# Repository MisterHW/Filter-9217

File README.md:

# Filter-9217

A pluggable input filter adapter to mitigate CM and DM noise on 4-wire RTD scanner modules like NI-9217.

## Schematic

## Board

## Connectors

For part names and mating connector see 
[Filter-9217-1A_sch.pdf](Filter-9217-1A/Filter-9217-1A_sch.pdf).

## Revisions

- 2021-03-09: Rev-1A released with corrected silk screen orientation (was upside-down when module mounted horizontally)

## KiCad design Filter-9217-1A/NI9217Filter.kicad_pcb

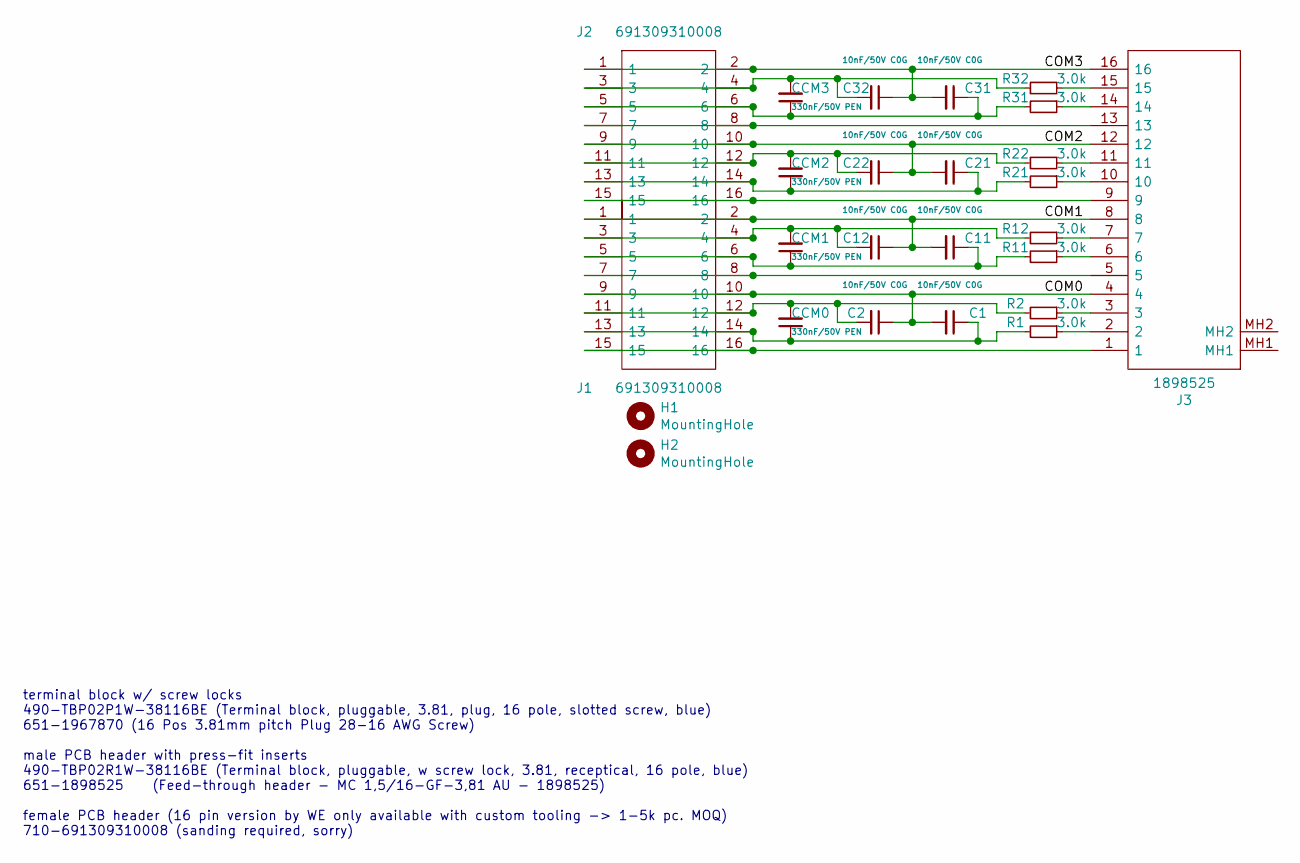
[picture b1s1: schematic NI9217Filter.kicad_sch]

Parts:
C1, C2, C11, C12, C21, C22, C31, C32: 10nF/50V C0G; C_0805_2012Metric; Mouser 791-0805N103J500CT
CCM0, CCM1, CCM2, CCM3: 330nF/50V PEN; C_2220_5650Metric; Mouser 80-LDECD3330KA5N00
H1, H2: MountingHole; MountingHole_3mm_Pad
J1, J2: 691309310008; Manufacturer_Part_Number 691309310008; Mouser Part Number 710-691309310008
J3: 1898525; Manufacturer_Part_Number 1898525; Mouser Part Number 651-1898525
R1, R2, R11, R12, R21, R22, R31, R32: 3.0k; R_0805_2012Metric; Mouser 667-ERJ-S06F3001V

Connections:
/COM0: C1.2, C2.1, J2.9, J2.10, J3.4
/COM1: C11.2, C12.1, J2.1, J2.2, J3.8
/COM2: C21.2, C22.1, J1.9, J1.10, J3.12
/COM3: C31.2, C32.1, J1.1, J1.2, J3.16
unnamed: C1.1, CCM0.1, J2.13, J2.14, R1.2
unnamed: C2.2, CCM0.2, J2.11, J2.12, R2.2
unnamed: C11.1, CCM1.1, J2.5, J2.6, R11.2
unnamed: C12.2, CCM1.2, J2.3, J2.4, R12.2
unnamed: C21.1, CCM2.1, J1.13, J1.14, R21.2
unnamed: C22.2, CCM2.2, J1.11, J1.12, R22.2
unnamed: C31.1, CCM3.1, J1.5, J1.6, R31.2
unnamed: C32.2, CCM3.2, J1.3, J1.4, R32.2
unnamed: J1.7, J1.8, J3.13
unnamed: J1.15, J1.16, J3.9
unnamed: J2.7, J2.8, J3.5
unnamed: J2.15, J2.16, J3.1
unnamed: J3.2, R1.1
unnamed: J3.3, R2.1
unnamed: J3.6, R11.1
unnamed: J3.7, R12.1
unnamed: J3.10, R21.1
unnamed: J3.11, R22.1
unnamed: J3.14, R31.1
unnamed: J3.15, R32.1

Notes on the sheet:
terminal block w/ screw locks 490-TBP02P1W-38116BE (Terminal block, pluggable, 3.81, plug, 16 pole, slotted screw, blue) 651-1967870 (16 Pos 3.81mm pitch Plug 28-16 AWG Screw) male PCB header with press-fit inserts 490-TBP02R1W-38116BE (Terminal block, pluggable, w screw lock, 3.81, receptical, 16 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

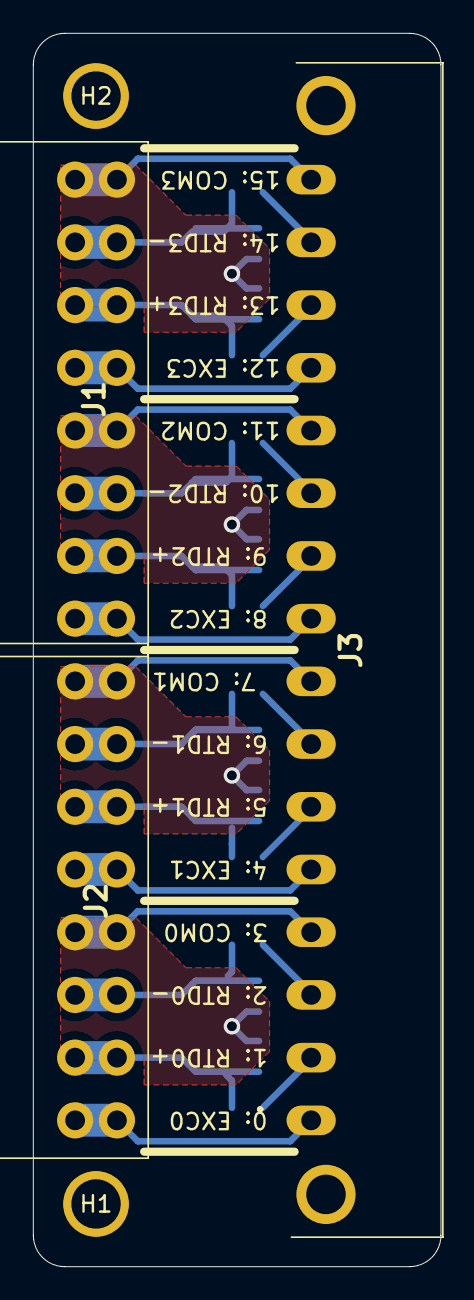
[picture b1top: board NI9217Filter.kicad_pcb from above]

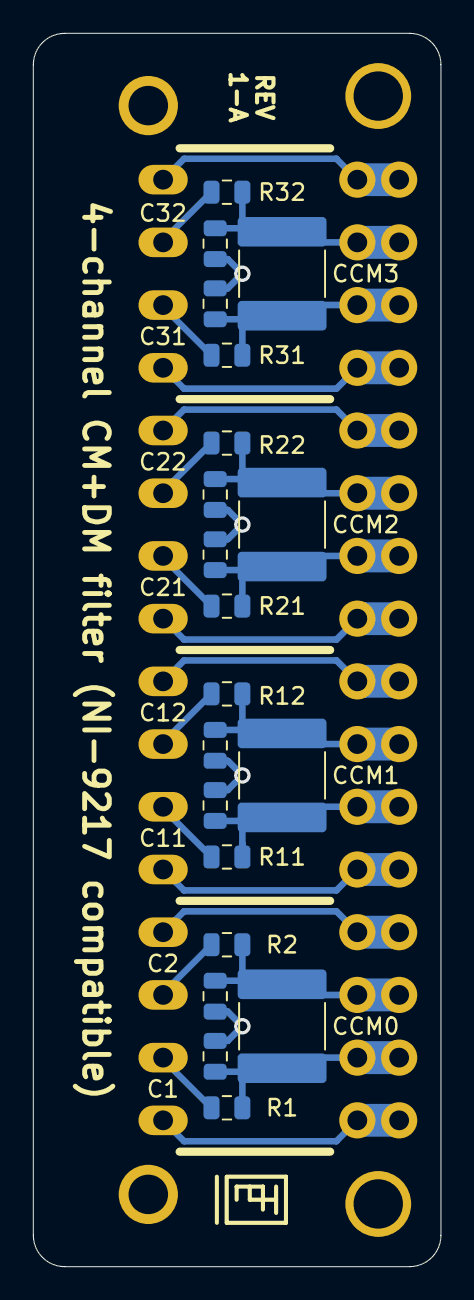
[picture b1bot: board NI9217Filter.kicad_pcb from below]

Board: 2 copper layers, 24.8 x 74.9 mm, 25 parts (20 on the bottom side), 24 nets.

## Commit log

2021-03-09 Release of rev-1A with clean-ups and corrected silk screen.
